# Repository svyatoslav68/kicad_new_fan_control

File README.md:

# kicad_new_fan_control
Термометр с управлением вентилятором

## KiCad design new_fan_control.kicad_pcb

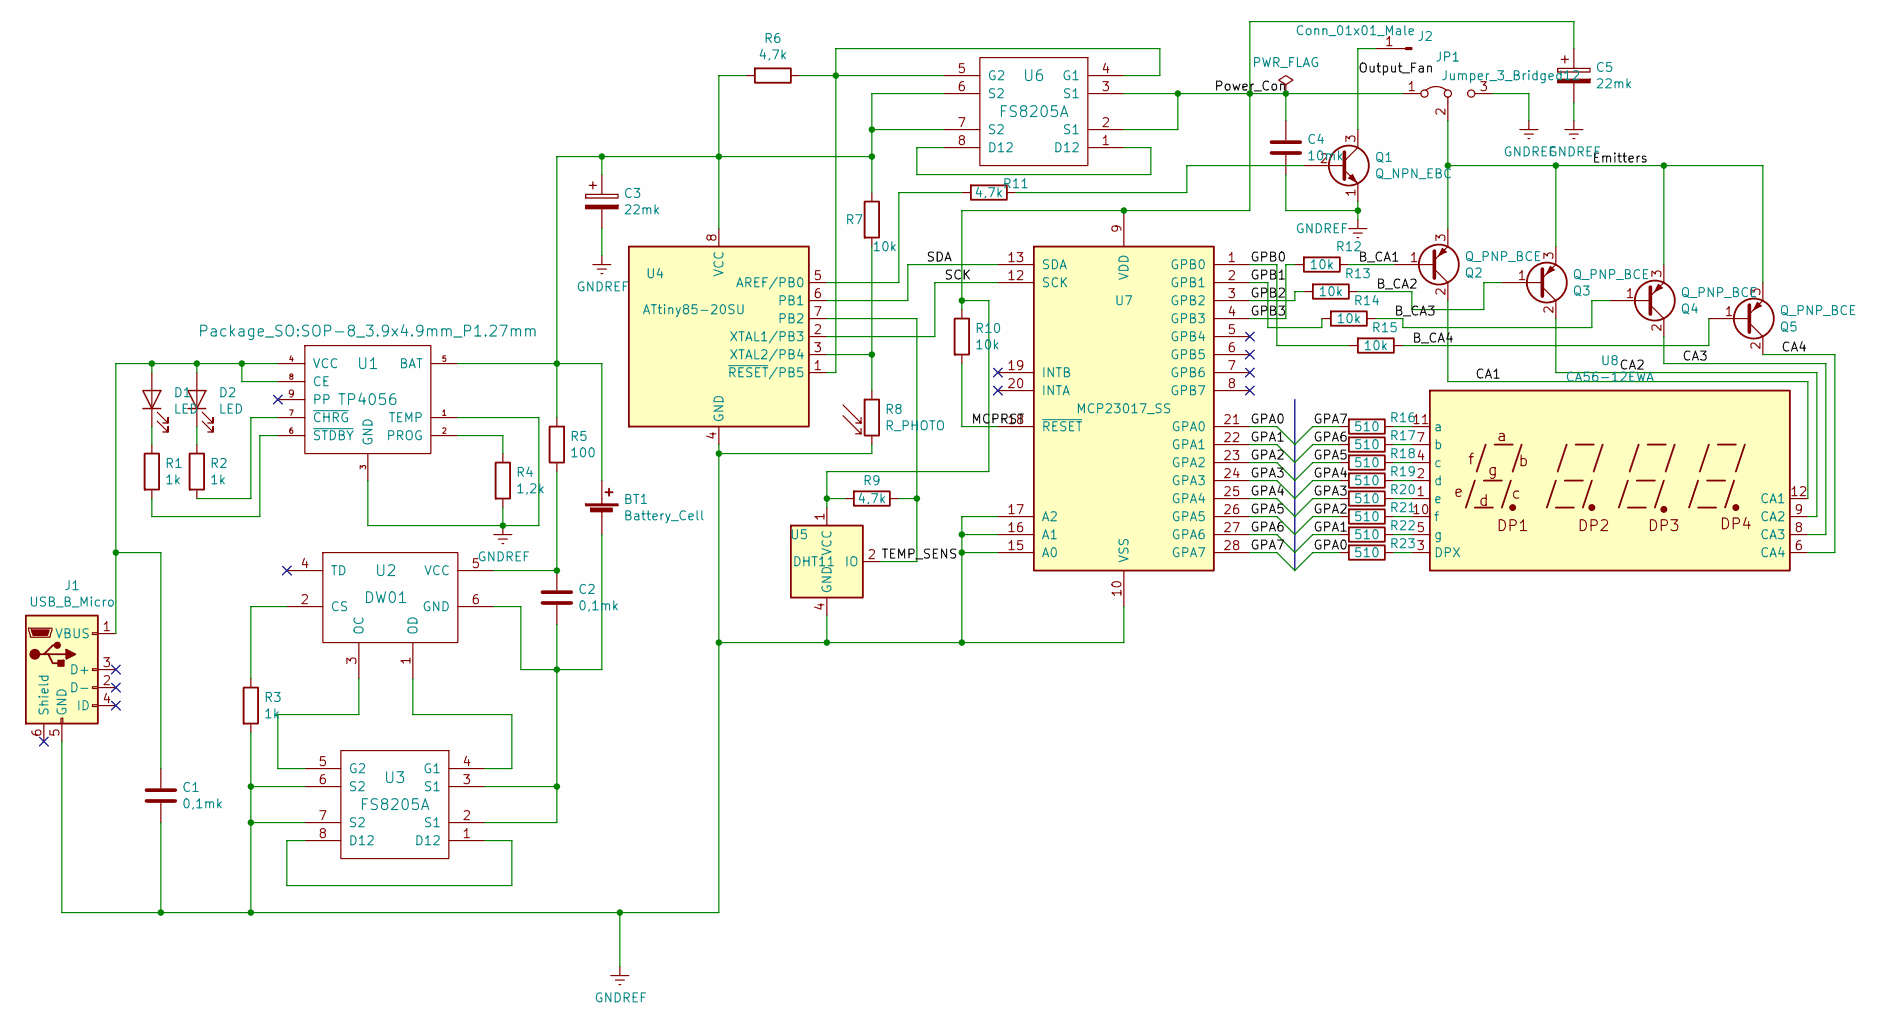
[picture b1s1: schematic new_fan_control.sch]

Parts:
BT1: Battery_Cell; BatteryHolder_MPD_BH-18650-PC2
C1, C2: 0,1mk; C_1206_3216Metric_Pad1.33x1.80mm_HandSolder
C3, C5: 22mk; CP_Radial_D5.0mm_P2.00mm
C4: 10mk; C_1206_3216Metric_Pad1.33x1.80mm_HandSolder
D1, D2: LED; LED_D3.0mm_FlatTop
J1: USB_B_Micro; USB_Micro-B_Wuerth_629105150521_CircularHoles
J2: Conn_01x01_Male; PinHeader_1x01_P2.54mm_Vertical
JP1: Jumper_3_Bridged12; Pin_Header_Straight_1x03_Pitch2.54mm
Q1: Q_NPN_EBC; SOT-23
Q2, Q3, Q4, Q5: Q_PNP_BCE; SOT-23
R1, R2, R3: 1k; R_1206_3216Metric_Pad1.30x1.75mm_HandSolder
R4: 1,2k; R_1206_3216Metric_Pad1.30x1.75mm_HandSolder
R5: 100; R_1206_3216Metric_Pad1.30x1.75mm_HandSolder
R6, R9, R11: 4,7k; R_1206_3216Metric_Pad1.30x1.75mm_HandSolder
R7, R10, R12, R13, R14, R15: 10k; R_1206_3216Metric_Pad1.30x1.75mm_HandSolder
R8: R_PHOTO; R_LDR_12x10.8mm_P9.0mm_Vertical
R16, R17, R18, R19, R20, R21, R22, R23: 510; R_1206_3216Metric_Pad1.30x1.75mm_HandSolder
U1: TP4056; SOP-8_3.9x4.9mm_P1.27mm
U2: DW01; SOT-23-6_Handsoldering
U3, U6: FS8205A; TSSOP-8_4.4x3mm_P0.65mm
U4: ATtiny85-20SU; SOIJ-8_5.3x5.3mm_P1.27mm
U5: DHT11; Aosong_DHT11_5.5x12.0_P2.54mm
U7: MCP23017_SS; SSOP-28_5.3x10.2mm_Pitch0.65mm
U8: CA56-12EWA

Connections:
/B_CA1: Q2.1 (B), R12.1
/B_CA2: Q3.1 (B), R13.1
/B_CA3: Q4.1 (B), R14.1
/B_CA4: Q5.1 (B), R15.1
/CA1: Q2.2 (C), U8.12 (CA1)
/CA2: Q3.2 (C), U8.9 (CA2)
/CA3: Q4.2 (C), U8.8 (CA3)
/CA4: Q5.2 (C), U8.6 (CA4)
/Emitters: JP1.2 (C), Q2.3 (E), Q3.3 (E), Q4.3 (E), Q5.3 (E)
/GPA0: R23.2, U7.21 (GPA0)
/GPA1: R22.2, U7.22 (GPA1)
/GPA2: R21.2, U7.23 (GPA2)
/GPA3: R20.2, U7.24 (GPA3)
/GPA4: R19.2, U7.25 (GPA4)
/GPA5: R18.2, U7.26 (GPA5)
/GPA6: R17.2, U7.27 (GPA6)
/GPA7: R16.2, U7.28 (GPA7)
/GPB0: R15.2, U7.1 (GPB0)
/GPB1: R14.2, U7.2 (GPB1)
/GPB2: R13.2, U7.3 (GPB2)
/GPB3: R12.2, U7.4 (GPB3)
/MCPRST: R10.2, U7.18 (~RESET~)
/Output_Fan: J2.1, Q1.3 (C)
/Power_Con: C4.1, C5.1, JP1.1 (A), R9.2, R10.1, U5.1 (VCC), U6.2 (S1), U6.3 (S1), U7.9 (VDD)
/SCK: U4.2 (XTAL1/PB3), U7.12 (SCK)
/SDA: U4.6 (PB1), U7.13 (SDA)
/TEMP_SENS: R9.1, U4.7 (PB2), U5.2 (IO)
GNDREF: C1.2, C3.2, C4.2, C5.2, J1.5 (GND), JP1.3 (B), Q1.1 (E), R3.2, R4.2, R8.2, U1.1 (TEMP), U1.3 (GND), U3.6 (S2), U3.7 (S2), U4.4 (GND), U5.4 (GND), U7.10 (VSS), U7.15 (A0), U7.16 (A1), U7.17 (A2); also elsewhere on the board
unnamed 28: BT1.1 (+), C3.1, R5.2, R6.2, R7.1, U1.5 (BAT), U4.8 (VCC), U6.6 (S2), U6.7 (S2); also elsewhere on the board
unnamed: BT1.2 (-), C2.2, U2.6 (GND), U3.2 (S1), U3.3 (S1)
unnamed: C1.1, D1.2 (A), D2.2 (A), J1.1 (VBUS), U1.4 (VCC), U1.8 (CE)
unnamed: C2.1, R5.1, U2.5 (VCC)
unnamed: D1.1 (K), R1.1
unnamed: D2.1 (K), R2.1
unnamed: Q1.2 (B), R11.1
unnamed: R1.2, U1.6 (~STDBY)
unnamed: R2.2, U1.7 (~CHRG)
unnamed: R3.1, U2.2 (CS)
unnamed: R4.1, U1.2 (PROG)
unnamed: R6.1, U4.1 (~RESET~/PB5), U6.4 (G1), U6.5 (G2)
unnamed: R7.2, R8.1, U4.3 (XTAL2/PB4)
unnamed: R11.2, U4.5 (AREF/PB0)
unnamed: R16.1, U8.11 (a)
unnamed: R17.1, U8.7 (b)
unnamed: R18.1, U8.4 (c)
unnamed: R19.1, U8.2 (d)
unnamed: R20.1, U8.1 (e)
unnamed: R21.1, U8.10 (f)
unnamed: R22.1, U8.5 (g)
unnamed: R23.1, U8.3 (DPX)
unnamed: U2.1 (OD), U3.4 (G1)
unnamed: U2.3 (OC), U3.5 (G2)
unnamed: U3.1 (D12), U3.8 (D12)
unnamed: U6.1 (D12), U6.8 (D12)

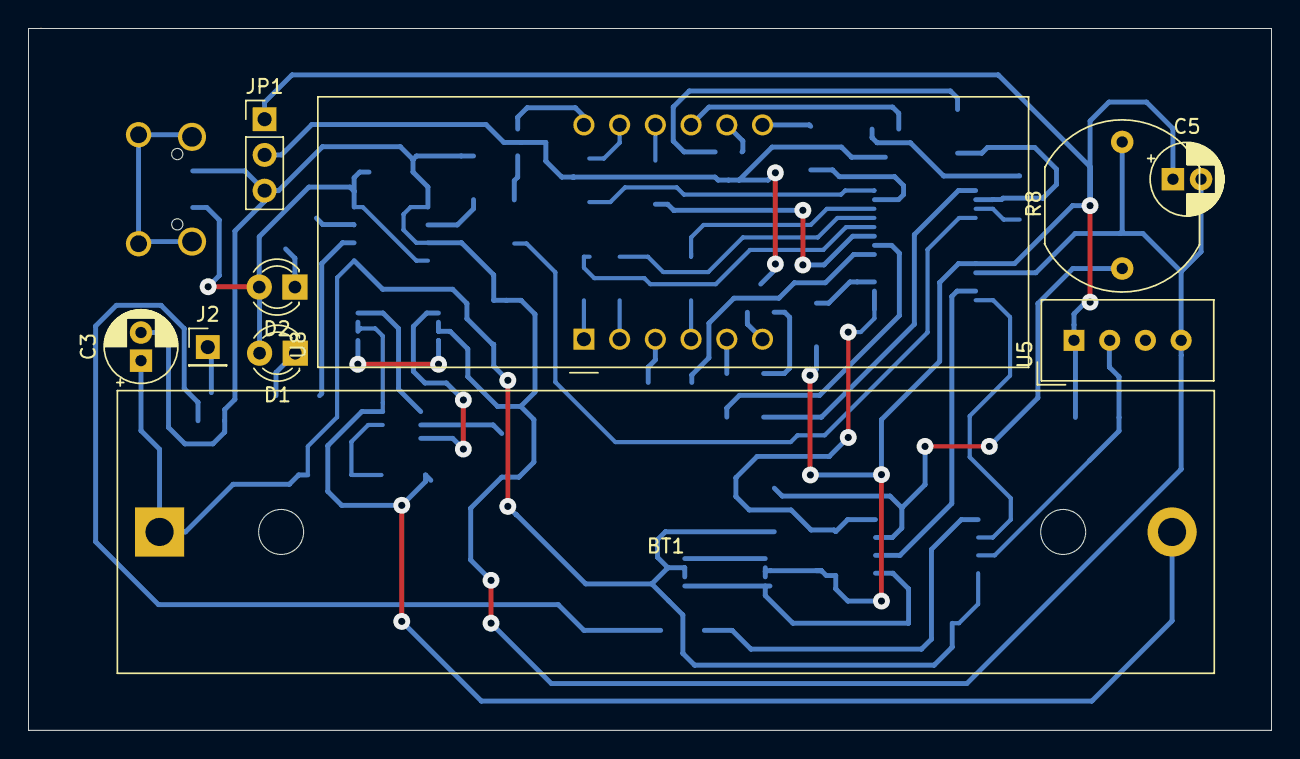
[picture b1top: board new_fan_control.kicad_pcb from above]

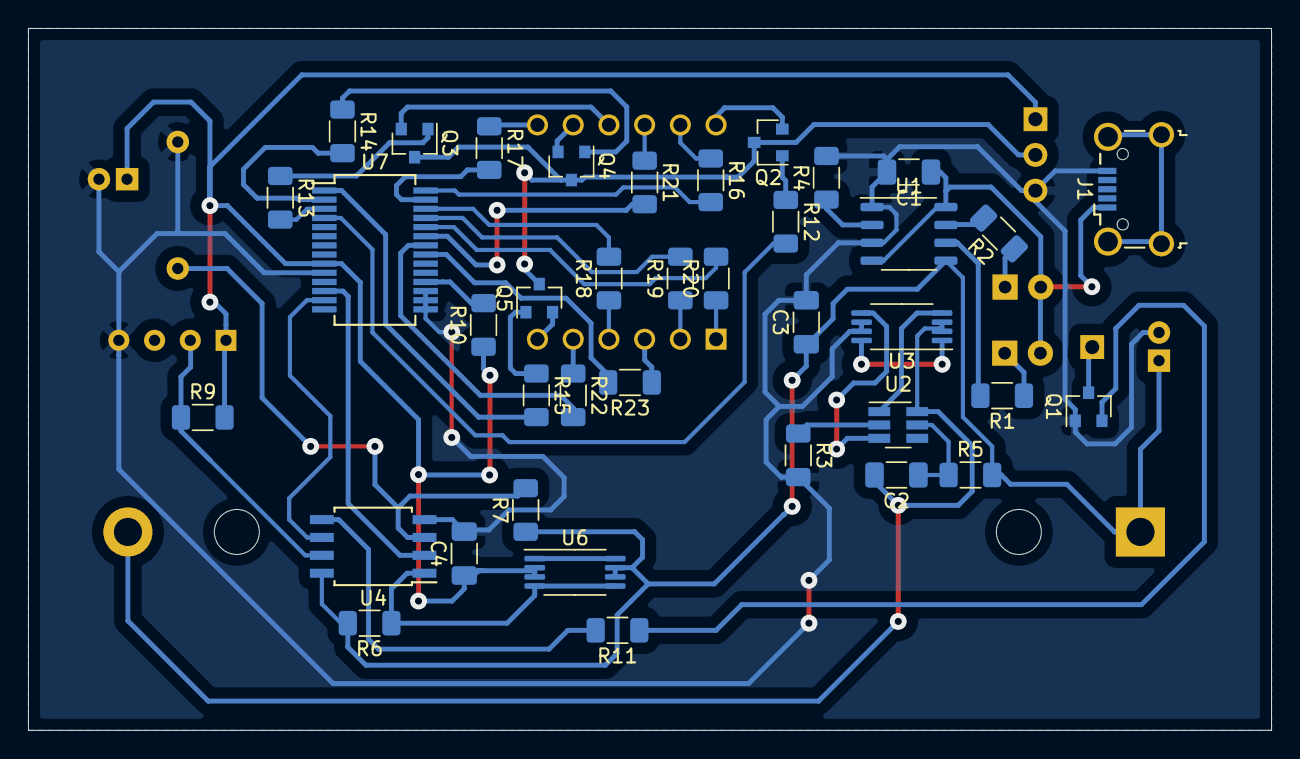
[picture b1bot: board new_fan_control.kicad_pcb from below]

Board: 2 copper layers, 88.4 x 49.9 mm, 48 parts (38 on the bottom side), 54 nets.

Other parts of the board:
C3#2: 22mk; CP_Radial_D5.0mm_P2.00mm

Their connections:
GNDREF: C3#2.2; also elsewhere on the board
unnamed 28: C3#2.1; also elsewhere on the board

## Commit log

2020-10-26 Version on 26.10.2020
